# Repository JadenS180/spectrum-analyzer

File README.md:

# ESP32 Audio Spectrum Analyzer

A real-time audio spectrum analyzer built on the ESP32, featuring a custom-designed PCB. Captures audio via an I2S MEMS microphone, runs FFT processing on-chip, displays a live 16-bar frequency spectrum on an OLED display, and streams real-time FFT data over WiFi to a browser-based visualizer via WebSockets.

---

## Demo Videos

**Analyzer reacting to noise:**

https://github.com/JadenS180/spectrum-analyzer/raw/main/media/spectrum-DemoNoise.MOV

**Analyzer in a quiet environment:**

https://github.com/JadenS180/spectrum-analyzer/raw/main/media/spectrum-DemoQuiet.MOV

---

## Web Dashboard

### Reacting to noise

### Quiet environment

---

## Photos

### Full Breadboard Build

### Side Views

### Components
| | |
|---|---|
|  |  |
| ESP32-WROOM-32 (front) | ESP32-WROOM-32 (back) |
|  |  |
| INMP441 Microphone (front) | INMP441 Microphone (back) |
|  |  |
| SSD1306 OLED (front) | SSD1306 OLED (back) |

### PCB

---

## Features

- Real-time FFT using 512-sample windows at 44,100 Hz
- 16 frequency bars mapped across the audible spectrum
- Hann windowing to reduce spectral leakage
- Peak hold indicators on each bar
- DC/low-frequency noise suppression via bin offset
- Custom 2-layer PCB designed in KiCad and manufactured by JLCPCB
- WiFi streaming via WebSockets to a browser-based canvas visualizer

---

## Hardware

| Component | Description |
|---|---|
| ESP32-WROOM-32 | Microcontroller |
| INMP441 | I2S MEMS microphone |
| SSD1306 | 0.91" I2C OLED display (128x32) |
| AMS1117-3.3 | 3.3V LDO voltage regulator |
| USB-C Receptacle | Power input |

### Pin Mapping

| Signal | ESP32 GPIO |
|---|---|
| I2S SCK | 26 |
| I2S WS | 25 |
| I2S SD | 33 |
| I2C SDA | 21 |
| I2C SCL | 22 |

---

## Firmware

Written in Arduino C++ using the Espressif ESP32 package (v3.3.10).

**Dependencies:**
- [arduinoFFT](https://github.com/kosme/arduinoFFT)
- [Adafruit SSD1306](https://github.com/adafruit/Adafruit_SSD1306)
- [Adafruit GFX Library](https://github.com/adafruit/Adafruit-GFX-Library)
- [WebSockets](https://github.com/Links2004/arduinoWebSockets)
- [ArduinoJson](https://github.com/bblanchon/ArduinoJson)

**To flash:**
1. Open firmware/spectrum_analyzer.ino in Arduino IDE
2. Set your WiFi credentials in the firmware
3. Select board: ESP32 Dev Module under Espressif Systems
4. Connect ESP32 via USB and select the correct port
5. Upload

---

## Web Dashboard

The dashboard is a single HTML file in the `dashboard/` directory. Open it in a browser while the ESP32 is powered and connected to WiFi. Update the WebSocket IP in `index.html` to match your ESP32's IP address.

---

## PCB Design

Designed in KiCad. The board is a 2-layer FR-4 PCB with a filled GND copper pour on F.Cu and a keep-out zone over the ESP32 antenna. Manufactured by JLCPCB.

KiCad schematic, PCB layout, and Gerber files are in the hardware/ directory.

---

## Repository Structure

```
spectrum-analyzer/
├── firmware/
│   └── spectrum_analyzer.ino
├── hardware/
│   ├── spectrum_analyzer.kicad_pro
│   ├── spectrum_analyzer.kicad_sch
│   ├── spectrum_analyzer.kicad_pcb
│   └── gerbers/
├── dashboard/
│   └── index.html
├── media/
│   ├── (photos)
│   └── (videos)
└── README.md
```

---

## Author

Jaden Smiles — [github.com/JadenS180](https://github.com/JadenS180)

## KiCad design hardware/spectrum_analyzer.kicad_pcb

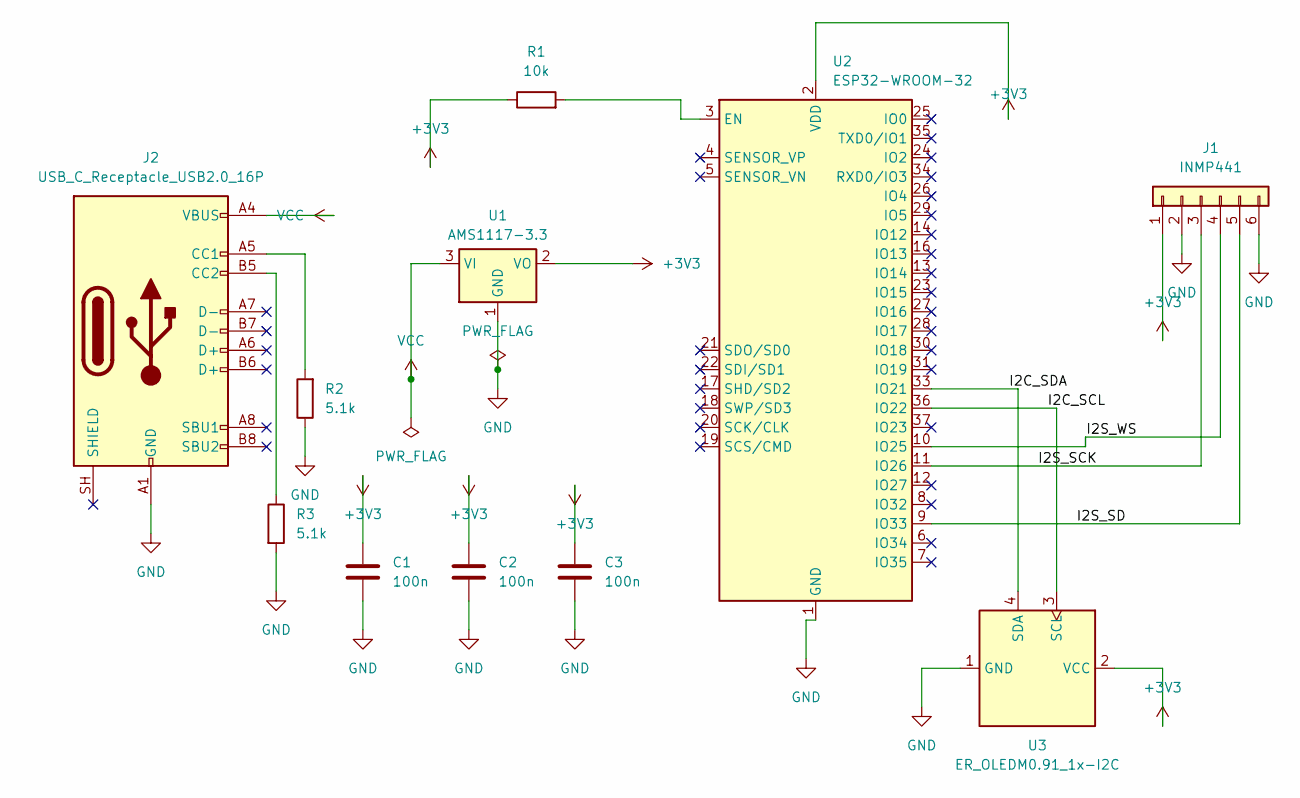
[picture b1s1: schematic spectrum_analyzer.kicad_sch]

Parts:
C1, C2, C3: 100n; C_0402_1005Metric
J1: INMP441; PinHeader_1x06_P2.54mm_Vertical
J2: USB_C_Receptacle_USB2.0_16P; USB_C_Receptacle_HRO_TYPE-C-31-M-12
R1: 10k; R_01005_0402Metric
R2, R3: 5.1k; R_01005_0402Metric
U1: AMS1117-3.3; SOT-223-3_TabPin2
U2: ESP32-WROOM-32
U3: ER_OLEDM0.91_1x-I2C

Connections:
+3V3: C1.1, C2.1, C3.1, J1.1, R1.1, U1.2 (VO), U2.2 (VDD), U3.2 (VCC)
/I2C_SCL: U2.36 (IO22), U3.3 (SCL)
/I2C_SDA: U2.33 (IO21), U3.4 (SDA)
/I2S_SCK: J1.3, U2.11 (IO26)
/I2S_SD: J1.5, U2.9 (IO33)
/I2S_WS: J1.4, U2.10 (IO25)
GND: C1.2, C2.2, C3.2, J1.2, J1.6, J2.A1 (GND), J2.A12 (GND), J2.B1 (GND), J2.B12 (GND), R2.1, R3.2, U1.1 (GND), U2.1 (GND), U2.15 (GND), U2.38 (GND), U2.39 (GND), U3.1 (GND)
unnamed: J2.A5 (CC1), R2.2
unnamed: J2.B5 (CC2), R3.1
unnamed: R1.2, U2.3 (EN)
VCC: J2.A4 (VBUS), J2.A9 (VBUS), J2.B4 (VBUS), J2.B9 (VBUS), U1.3 (VI)

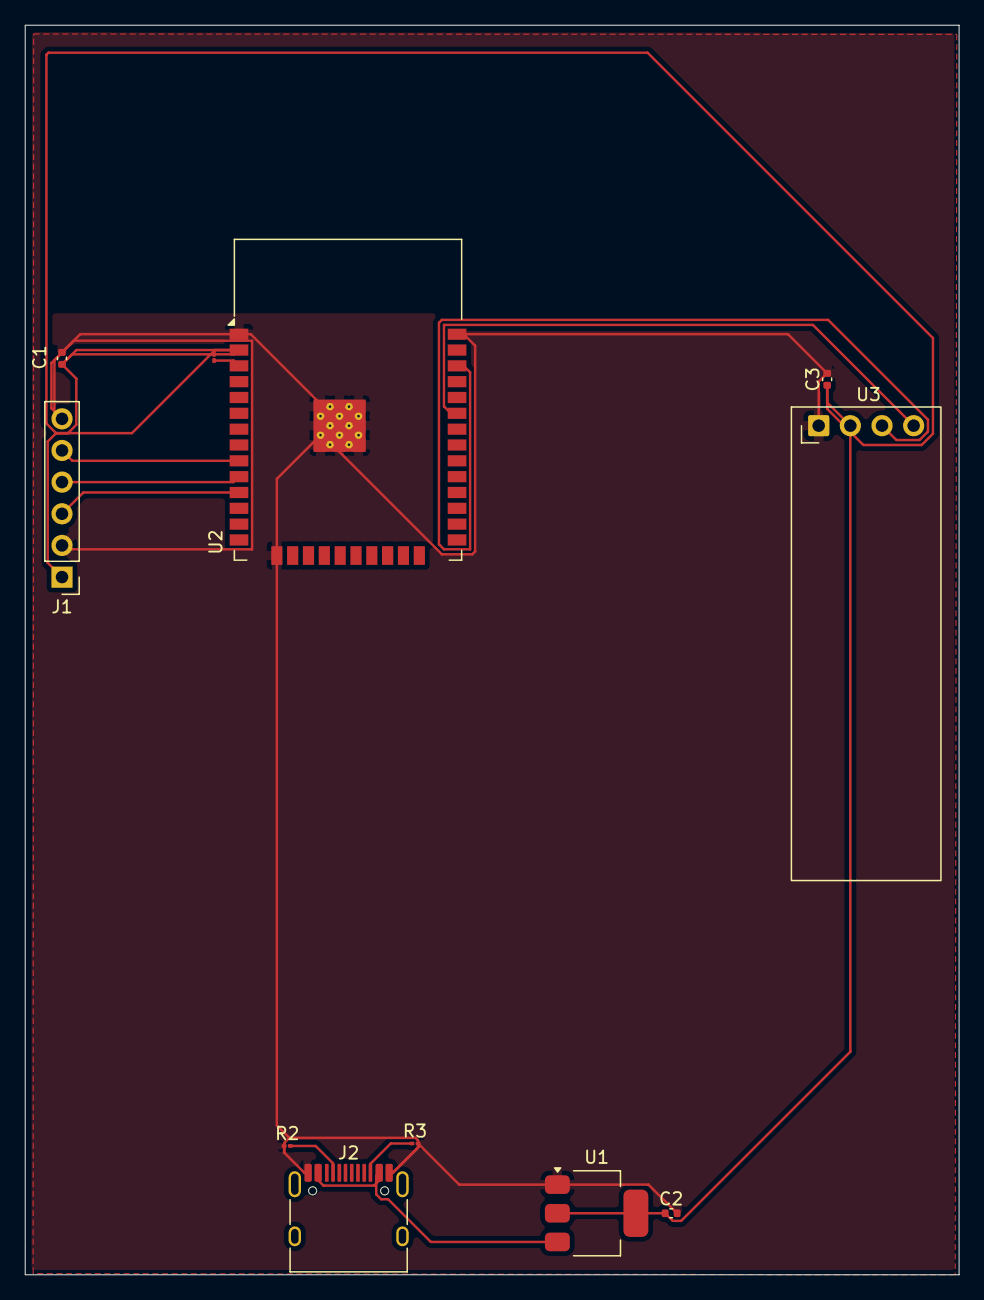
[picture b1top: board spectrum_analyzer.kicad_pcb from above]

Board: 2 copper layers, 74.9 x 100.3 mm, 11 parts (0 on the bottom side), 11 nets.

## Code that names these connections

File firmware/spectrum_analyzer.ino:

/*
  Blink

  Turns an LED on for one second, then off for one second, repeatedly.

  Most Arduinos have an on-board LED you can control. On the UNO, MEGA and ZERO
  it is attached to digital pin 13, on MKR1000 on pin 6. LED_BUILTIN is set to
  the correct LED pin independent of which board is used.
  If you want to know what pin the on-board LED is connected to on your Arduino
  model, check the Technical Specs of your board at:
  https://docs.arduino.cc/hardware/

  modified 8 May 2014
  by Scott Fitzgerald
  modified 2 Sep 2016
  by Arturo Guadalupi
  modified 8 Sep 2016
  by Colby Newman

  This example code is in the public domain.

  https://docs.arduino.cc/built-in-examples/basics/Blink/
*/

#include <driver/i2s.h>
#include <arduinoFFT.h>
#include <Wire.h>
#include <Adafruit_GFX.h>
#include <Adafruit_SSD1306.h>

// Display
#define SCREEN_WIDTH 128
#define SCREEN_HEIGHT 64
#define OLED_RESET -1
Adafruit_SSD1306 display(SCREEN_WIDTH, SCREEN_HEIGHT, &Wire, OLED_RESET);

// I2S pins
#define I2S_WS  25
#define I2S_SCK 26
#define I2S_SD  33

// FFT
#define SAMPLE_RATE     44100
#define FFT_SAMPLES     512
#define NUM_BARS        16
#define DISPLAY_HEIGHT  54  // leave room for labels

double vReal[FFT_SAMPLES];
double vImag[FFT_SAMPLES];

ArduinoFFT<double> FFT = ArduinoFFT<double>(vReal, vImag, FFT_SAMPLES, SAMPLE_RATE);

// Peak hold
int peaks[NUM_BARS] = {0};
int peakHoldTimer[NUM_BARS] = {0};
#define PEAK_HOLD_FRAMES 20
#define PEAK_DECAY 1

void setup() {
  Serial.begin(115200);

  // Init display
  if (!display.begin(SSD1306_SWITCHCAPVCC, 0x3C)) {
    Serial.println("SSD1306 not found");
    while (true);
  }
  display.clearDisplay();
  display.display();

  // Init I2S
  i2s_config_t i2s_config = {
    .mode = (i2s_mode_t)(I2S_MODE_MASTER | I2S_MODE_RX),
    .sample_rate = SAMPLE_RATE,
    .bits_per_sample = I2S_BITS_PER_SAMPLE_32BIT,
    .channel_format = I2S_CHANNEL_FMT_ONLY_LEFT,
    .communication_format = I2S_COMM_FORMAT_STAND_I2S,
    .intr_alloc_flags = ESP_INTR_FLAG_LEVEL1,
    .dma_buf_count = 8,
    .dma_buf_len = FFT_SAMPLES,
    .use_apll = false,
    .tx_desc_auto_clear = false,
    .fixed_mclk = 0
  };

  i2s_pin_config_t pin_config = {
    .bck_io_num = I2S_SCK,
    .ws_io_num = I2S_WS,
    .data_out_num = I2S_PIN_NO_CHANGE,
    .data_in_num = I2S_SD
  };

  i2s_driver_install(I2S_NUM_0, &i2s_config, 0, NULL);
  i2s_set_pin(I2S_NUM_0, &pin_config);
}

void loop() {
  // Read samples from I2S
  int32_t rawSamples[FFT_SAMPLES];
  size_t bytes_read;
  i2s_read(I2S_NUM_0, rawSamples, sizeof(rawSamples), &bytes_read, portMAX_DELAY);

  // Convert to doubles and apply Hann window
  for (int i = 0; i < FFT_SAMPLES; i++) {
    vReal[i] = (double)(rawSamples[i] >> 8);
    vImag[i] = 0.0;
  }

  // Run FFT
  FFT.windowing(FFTWindow::Hann, FFTDirection::Forward);
  FFT.compute(FFTDirection::Forward);
  FFT.complexToMagnitude();

  // Map FFT bins to display bars
  int barWidth = SCREEN_WIDTH / NUM_BARS;
  int binSize = (FFT_SAMPLES / 2) / NUM_BARS;

  display.clearDisplay();

  for (int bar = 0; bar < NUM_BARS; bar++) {
    // Average magnitude across bins for this bar
    double sum = 0;
    int binOffset = 4;  
    for (int bin = 0; bin < binSize; bin++) {
      sum += vReal[bar * binSize + bin + binOffset];
    }
    double avg = sum / binSize;

    // Scale to display height
    int barHeight = (int)(avg / 300000.0 * DISPLAY_HEIGHT);
    barHeight = constrain(barHeight, 0, DISPLAY_HEIGHT);

    int x = bar * barWidth;
    int y = DISPLAY_HEIGHT - barHeight;

    // Draw bar
    display.fillRect(x + 1, y, barWidth - 2, barHeight, SSD1306_WHITE);

    // Peak hold
    if (barHeight >= peaks[bar]) {
      peaks[bar] = barHeight;
      peakHoldTimer[bar] = PEAK_HOLD_FRAMES;
    } else {
      if (peakHoldTimer[bar] > 0) {
        peakHoldTimer[bar]--;
      } else {
        peaks[bar] = max(0, peaks[bar] - PEAK_DECAY);
      }
    }

    // Draw peak dot
    int peakY = DISPLAY_HEIGHT - peaks[bar];
    if (peaks[bar] > 0) {
      display.drawFastHLine(x + 1, peakY, barWidth - 2, SSD1306_WHITE);
    }
  }

  display.display();
}

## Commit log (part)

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2026-06-28 Initial commit: firmware and PCB design files
2026-06-28 Revise README for ESP32 Audio Spectrum Analyzer
    Updated README to provide detailed project description, features, hardware specifications, firmware instructions, PCB design information, and repository structure.
2026-06-29 Added breadboard prototype photos and demo videos
2026-06-29 Updated README with photos, videos, and project details
2026-06-29 Fixed README content
2026-06-29 Fix formatting of code block in README.md
